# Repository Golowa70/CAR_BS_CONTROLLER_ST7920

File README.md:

# CAR_BS_CONTROLLER_ST7920
Контроллер дополнительного 
оборудования автомобиля описанного в https://github.com/Golowa70/CAR-BS-CONTROLLER-NEX
Используется то же железо но вместо nextion применён дисплей ST7920 + три кнопки
для навигации по меню.

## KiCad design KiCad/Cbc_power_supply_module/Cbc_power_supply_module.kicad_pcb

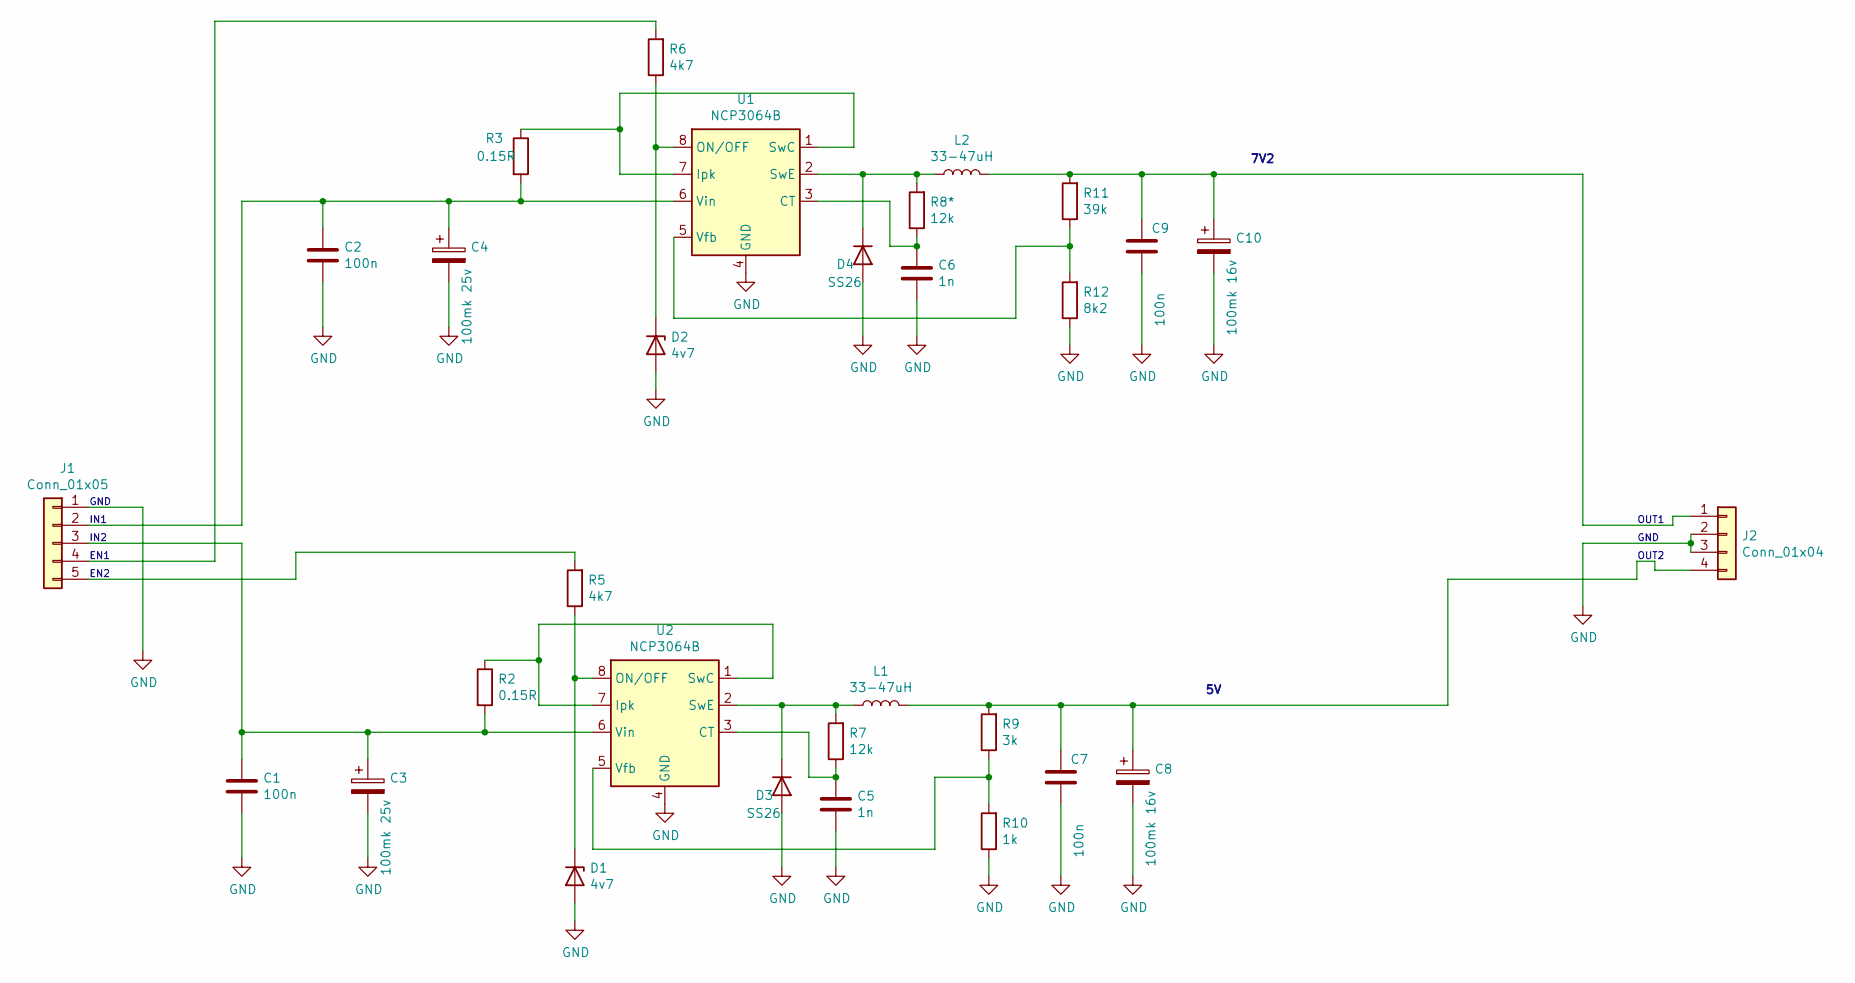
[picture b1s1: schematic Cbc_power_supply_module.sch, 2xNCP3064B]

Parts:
C1, C2, C7, C9: 100n; C_0805_2012Metric_Pad1.18x1.45mm_HandSolder
C3, C4: 100mk 25v; CP_Radial_D8.0mm_P3.80mm
C5, C6: 1n; C_0805_2012Metric_Pad1.18x1.45mm_HandSolder
C8, C10: 100mk 16v; CP_Radial_D8.0mm_P3.80mm
D1, D2: 4v7; D_MiniMELF
D3, D4: SS26; D_SMB
J1: Conn_01x05; PinHeader_1x05_P2.54mm_Vertical
J2: Conn_01x04; PinHeader_1x04_P2.54mm_Vertical
L1, L2: 33-47uH; L_7.3x7.3_H4.5
R2, R3: 0.15R; R_1210_3225Metric_Pad1.30x2.65mm_HandSolder
R5, R6: 4k7; R_0603_1608Metric_Pad0.98x0.95mm_HandSolder
R7, R8*: 12k; R_0805_2012Metric_Pad1.20x1.40mm_HandSolder
R9: 3k; R_0805_2012Metric_Pad1.20x1.40mm_HandSolder
R10: 1k; R_0805_2012Metric_Pad1.20x1.40mm_HandSolder
R11: 39k; R_0805_2012Metric_Pad1.20x1.40mm_HandSolder
R12: 8k2; R_0805_2012Metric_Pad1.20x1.40mm_HandSolder
U1, U2: NCP3064B; SOIC-8_3.9x4.9mm_P1.27mm

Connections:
GND: C1.2, C2.2, C3.2, C4.2, C5.2, C6.2, C7.2, C8.2, C9.2, C10.2, D1.2 (A), D2.2 (A), D3.2 (A), D4.2 (A), J1.1, J2.2, J2.3, R10.1, R12.1, U1.4 (GND), U2.4 (GND)
unnamed: C1.1, C3.1, J1.3, R2.2, U2.6 (Vin)
unnamed: C2.1, C4.1, J1.2, R3.2, U1.6 (Vin)
unnamed: C5.1, R7.1, U2.3 (CT)
unnamed 4: C6.1, R8*.1, U1.3 (CT); also elsewhere on the board
unnamed: C7.1, C8.1, J2.4, L1.2, R9.2
unnamed: C9.1, C10.1, J2.1, L2.2, R11.2
unnamed: D1.1 (K), R5.1, U2.8 (ON/OFF)
unnamed: D2.1 (K), R6.1, U1.8 (ON/OFF)
unnamed: D3.1 (K), L1.1, R7.2, U2.2 (SwE)
unnamed 10: D4.1 (K), L2.1, R8*.2, U1.2 (SwE); also elsewhere on the board
unnamed: J1.4, R6.2
unnamed: J1.5, R5.2
unnamed: R2.1, U2.1 (SwC), U2.7 (Ipk)
unnamed: R3.1, U1.1 (SwC), U1.7 (Ipk)
unnamed: R9.1, R10.2, U2.5 (Vfb)
unnamed: R11.1, R12.2, U1.5 (Vfb)

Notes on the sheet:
7V2
GND
IN1
OUT1
EN1
IN2
OUT2
EN2

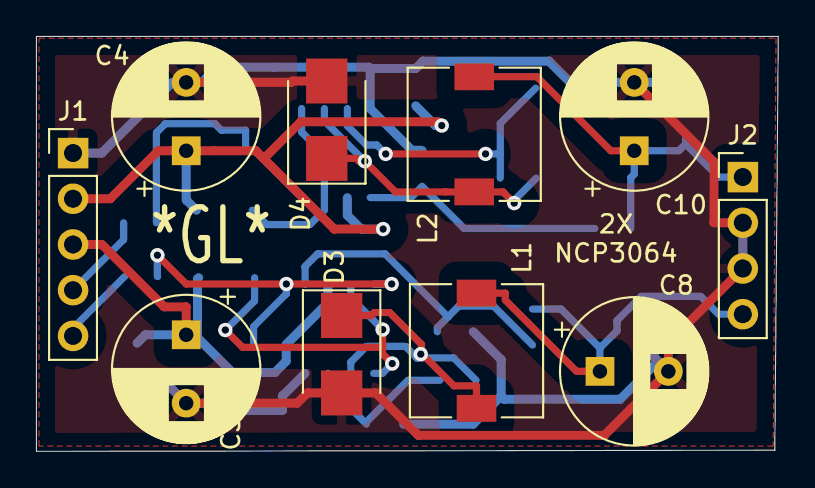
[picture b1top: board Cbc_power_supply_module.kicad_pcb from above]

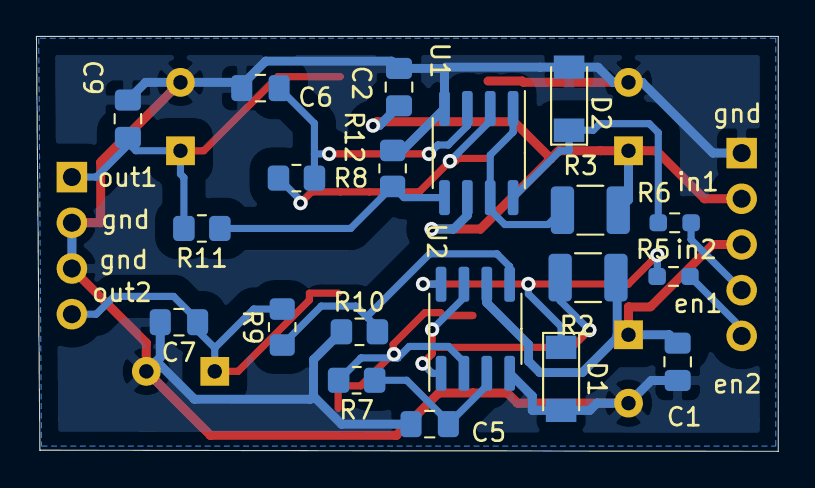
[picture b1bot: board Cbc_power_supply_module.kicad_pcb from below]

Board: 2 copper layers, 41.2 x 23.1 mm, 30 parts (20 on the bottom side), 17 nets.

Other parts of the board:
R8: 12k; R_0805_2012Metric_Pad1.20x1.40mm_HandSolder

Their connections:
unnamed 4: R8.1; also elsewhere on the board
unnamed 10: R8.2; also elsewhere on the board

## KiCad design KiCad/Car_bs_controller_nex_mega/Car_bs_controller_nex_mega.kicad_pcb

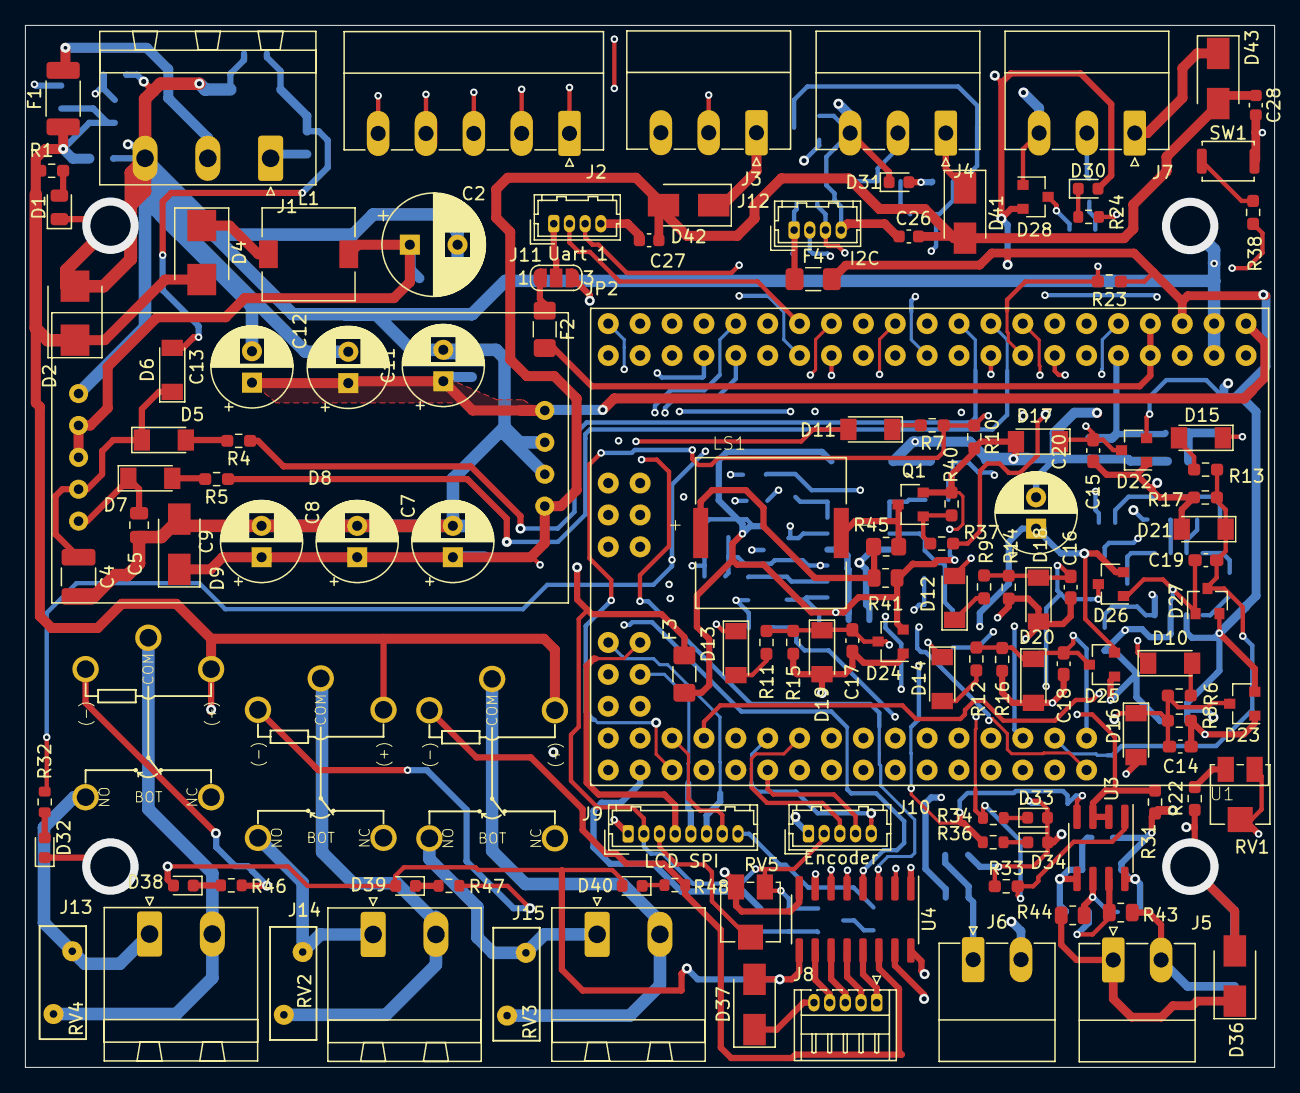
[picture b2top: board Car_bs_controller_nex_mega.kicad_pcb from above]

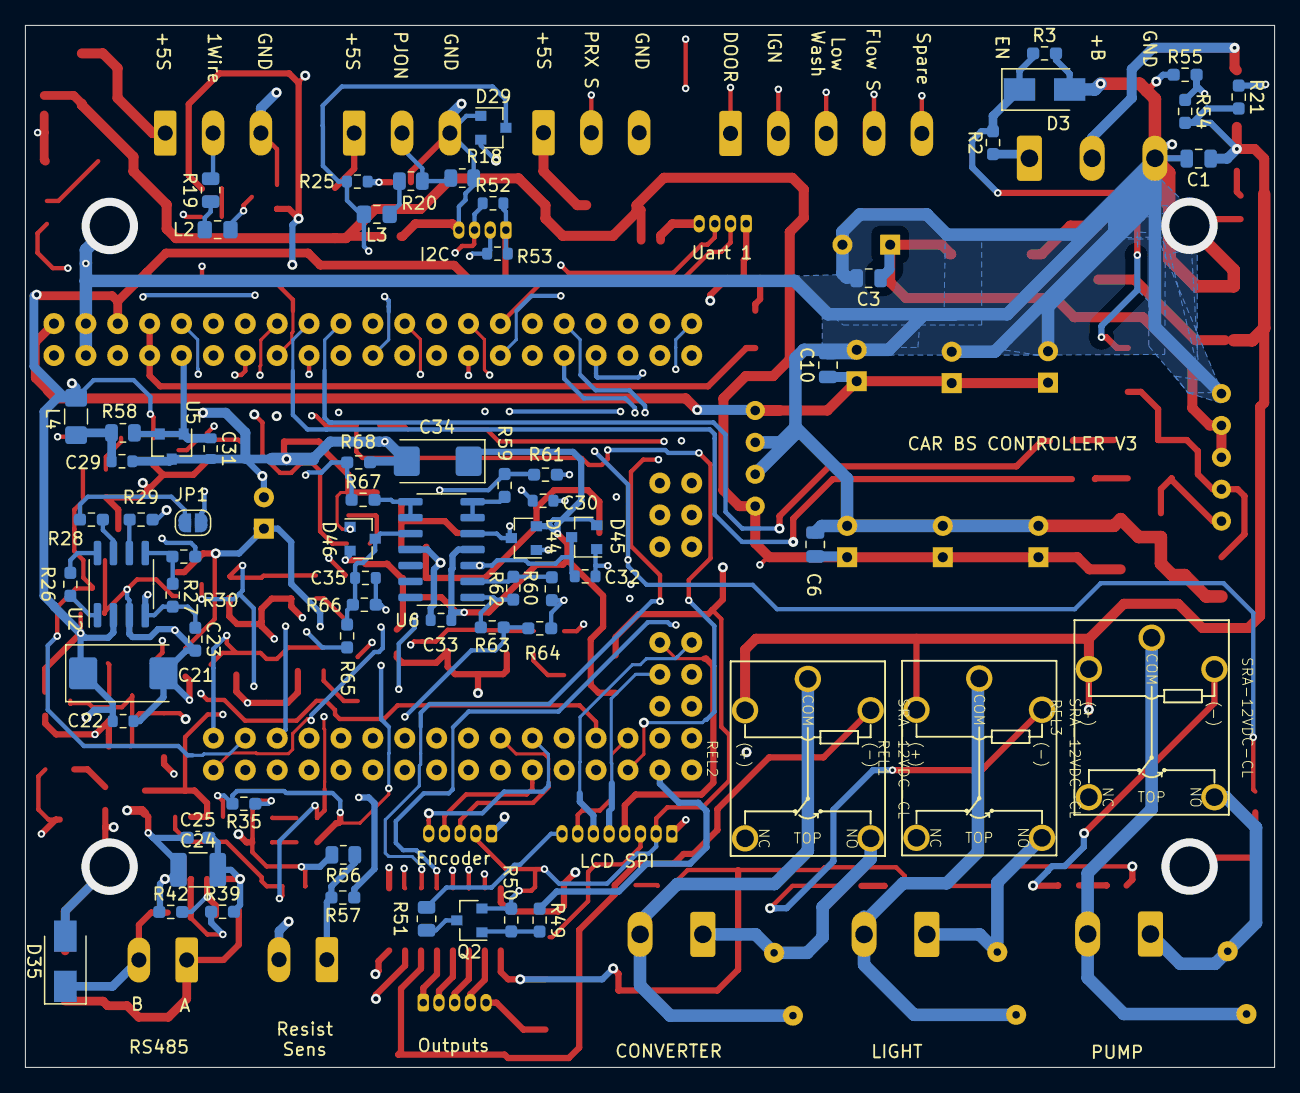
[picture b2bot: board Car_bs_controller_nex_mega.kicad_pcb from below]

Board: 4 copper layers, 99.5 x 83.0 mm, 192 parts (68 on the bottom side), 132 nets.

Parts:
C1, C3, C6, C10: 100n; C_0805_2012Metric
C2: 220mk 25v; CP_Radial_D8.0mm_P3.80mm
C4: 10mk; C_1210_3225Metric_Pad1.33x2.70mm_HandSolder
C5: 1n; C_0805_2012Metric
C7, C8, C9, C20: 220mk 10v; CP_Radial_D6.3mm_P2.50mm
C11, C12, C13: 220mk 16v; CP_Radial_D6.3mm_P2.50mm
C14, C15, C16, C17, C18, C19: 10n; C_0603_1608Metric_Pad1.08x0.95mm_HandSolder
C21: 10mk; CP_EIA-7343-15_Kemet-W_Pad2.25x2.55mm_HandSolder
C22, C29, C31, C33: 100n; R_0603_1608Metric
C23: 1n; R_0603_1608Metric_Pad0.98x0.95mm_HandSolder
C24: 10m; C_1210_3225Metric_Pad1.33x2.70mm_HandSolder
C25: 100n; C_0603_1608Metric_Pad1.08x0.95mm_HandSolder
C26, C27, C28: 100n; C_0603_1608Metric
C30, C32, C35: 10n; R_0603_1608Metric
C34: 10mk; CP_EIA-6032-15_Kemet-U
D1: PWR; LED_0805_2012Metric
D2: SMBJ18CA; D_SMB
D3: SMAJ18CA; D_SMA
D4: SS54; D_SMB
D5, D6, D7: 1N4148; D_MiniMELF
D8: Cbc_power_module
D9: SMBJ5CA; D_SMA
D10, D11, D12, D13, D14, D15: LL4148; D_MiniMELF
D16, D19, D20, D21: N; D_MiniMELF
D17, D18: 4V7; D_MiniMELF
D22, D23, D24, D25, D26, D27, D28, D29, D44, D45, D46: BAV99; SOT-23
D30: LED_1WIRE; LED_0603_1608Metric
D31, D32: LED_PJ; LED_0603_1608Metric
D33, D34: LED; LED_0603_1608Metric
D35, D36: SMAJ5.0CA; D_SMA
D37, D41, D42, D43: SS14; D_SMA
D38: LED_K1; LED_0603_1608Metric
D39: LED_K2; LED_0603_1608Metric
D40: LED_K3; LED_0603_1608Metric
F1: 3A; Fuse_2010_5025Metric
F2, F3, F4: 200mA 5v; Fuse_1206_3216Metric_Pad1.42x1.75mm_HandSolder
J1: Power; PhoenixContact_MSTBA_2,5_3-G_1x03_P5.00mm_Horizontal
J2: Inputs; PhoenixContact_MC_1,5_5-G-3.81_1x05_P3.81mm_Horizontal
J3: Proxy; PhoenixContact_MC_1,5_3-G-3.81_1x03_P3.81mm_Horizontal
J4: PJON; PhoenixContact_MC_1,5_3-G-3.81_1x03_P3.81mm_Horizontal
J5: RS485; PhoenixContact_MC_1,5_2-G-3.81_1x02_P3.81mm_Horizontal
J6: RES_SENS; PhoenixContact_MC_1,5_2-G-3.81_1x02_P3.81mm_Horizontal
J7: 1_WARE; PhoenixContact_MC_1,5_3-G-3.81_1x03_P3.81mm_Horizontal
J8: Outputs; Hirose_DF13-05P-1.25DS_1x05_P1.25mm_Horizontal
J9: LCD_ST7920; Hirose_DF13-08P-1.25DSA_1x08_P1.25mm_Vertical
J10: Encoder; Hirose_DF13-05P-1.25DSA_1x05_P1.25mm_Vertical
J11: LCD_Nextion; Hirose_DF13-04P-1.25DSA_1x04_P1.25mm_Vertical
J12: I2C; Hirose_DF13-04P-1.25DSA_1x04_P1.25mm_Vertical
J13: PUMP_RELAY; PhoenixContact_MSTBA_2,5_2-G_1x02_P5.00mm_Horizontal
J14: LIGHT_RELAY; PhoenixContact_MSTBA_2,5_2-G_1x02_P5.00mm_Horizontal
J15: CONVERTER_RELAY; PhoenixContact_MSTBA_2,5_2-G_1x02_P5.00mm_Horizontal
JP1: SolderJumper_2_Open; SolderJumper-2_P1.3mm_Open_RoundedPad1.0x1.5mm
JP2: SolderJumper_3_Open; SolderJumper-3_P1.3mm_Open_RoundedPad1.0x1.5mm_NumberLabels
L1: 47uH; L_7.3x7.3_H4.5
L2, L3: BLN; L_0805_2012Metric_Pad1.15x1.40mm_HandSolder
L4: FB; L_1206_3216Metric_Pad1.42x1.75mm_HandSolder
LS1: PKLCS1212E4001-R1; SPKR_PKLCS1212E4001-R1
Q1: BSS138; SOT-23
Q2: BC857; SOT-23
R1: 3k9; R_0603_1608Metric_Pad0.98x0.95mm_HandSolder
R2, R4, R5: 2k; R_0603_1608Metric_Pad0.98x0.95mm_HandSolder
R3, R30, R37, R49: 1k; R_0603_1608Metric_Pad0.98x0.95mm_HandSolder
R6, R11, R12, R13, R23: 4k7; R_0603_1608Metric_Pad0.98x0.95mm_HandSolder
R7, R9: 15k; R_0603_1608Metric_Pad0.98x0.95mm_HandSolder
R8, R15, R16, R17: N; R_0603_1608Metric_Pad0.98x0.95mm_HandSolder
R10, R14, R31, R33, R35, R40, R50, R55, R57, R61, R66, R68: 10k; R_0603_1608Metric_Pad0.98x0.95mm_HandSolder
R18: 1M; R_0805_2012Metric
R19, R41: 22R; R_0805_2012Metric
R20: 180R; R_0805_2012Metric
R21, R65: 22k; R_0603_1608Metric_Pad0.98x0.95mm_HandSolder
R22, R29, R60: 2k2; R_0603_1608Metric_Pad0.98x0.95mm_HandSolder
R24, R25, R32, R52, R53: 2k2; R_0603_1608Metric
R26: 200R; R_0603_1608Metric_Pad0.98x0.95mm_HandSolder
R27: (not used) 1k; R_0603_1608Metric_Pad0.98x0.95mm_HandSolder
R28: 220R; R_0603_1608Metric_Pad0.98x0.95mm_HandSolder
R34, R36: 1k; R_0603_1608Metric
R38: 470R; R_0603_1608Metric_Pad0.98x0.95mm_HandSolder
R39, R42: 20k; R_0603_1608Metric_Pad0.98x0.95mm_HandSolder
R43, R44: 10R; R_0805_2012Metric
R45: 1k; R_0805_2012Metric_Pad1.20x1.40mm_HandSolder
R46, R47, R48: 10k; R_0603_1608Metric
R51: 220R; R_0805_2012Metric
R54: 39k; R_0603_1608Metric_Pad0.98x0.95mm_HandSolder
R56: 2k*; R_0805_2012Metric
R58: 330R; R_0805_2012Metric
R59, R63, R67: 6k8; R_0603_1608Metric_Pad0.98x0.95mm_HandSolder
R62: 10k*; R_0603_1608Metric_Pad0.98x0.95mm_HandSolder
R64: 15k*; R_0603_1608Metric_Pad0.98x0.95mm_HandSolder
REL1, REL2, REL3: SRA-12VDC-CL; AB2_SRA-12VDC-CL
RV1, RV5: 10k; Potentiometer_Bourns_3314J_Vertical
RV2, RV3, RV4: S07K17; RV_Disc_D9mm_W3.7mm_P5mm
SW1: SW_Push; SW_Push_SPST_NO_Alps_SKRK
U1: MEGA_PRO_EMBED_CH340G___ATMEGA2560; _ATMEGA2560
U2: ADM705; SOIC-8_3.9x4.9mm_P1.27mm
U3: MAX485E; SOIC-8_3.9x4.9mm_P1.27mm
U4: ULN2003A; SOIC-16_3.9x9.9mm_P1.27mm
U5: TL431DBZ; SOT-23
U6: MCP6004(LM324); SOIC-14_3.9x8.7mm_P1.27mm

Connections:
5V_sensors_stab: C6.1, C7.1, C8.1, C9.1, C26.1, C27.1, C28.1, D8.9, D9.1, D41.1, D42.1, D43.1, R65.2
7.2V_stab: C10.1, C11.1, C12.1, C13.1, D8.6, U1.VIN_1
+3v3_from_MCU: F2.2, U1.3V3_1, U1.3V3_2
+5v_FROM_MCU: C20.1, C21.1, C22.1, C24.1, C25.1, C33.1, C34.1, D22.2, D23.2, D24.2, D25.2, D26.2, D27.2, D28.2, D29.2, D30.2, D33.2, D34.2, D44.2, D45.2, D46.2, F3.2, F4.2, L4.1, R23.1, R31.1, R33.1, R35.1, R41.2, R42.1, R56.2, U1.5V_1, U2.2, U3.8, U6.4
+12V: C1.1, D2.1, D4.2, D37.1, D38.2, D39.2, D40.2, F1.1, R1.2, R21.2, R54.2, REL1.1, REL2.1, REL3.1, U4.9
CONVERTER_RELAY_COM: J15.2, REL2.3, RV3.1
CONVERTER_RELAY_NO: J15.1, REL2.5, RV3.2
DOOR_SWITCH_INPUT: D13.1, J2.1
GND: C1.2, C2.2, C3.2, C4.2, C5.2, C6.2, C7.2, C8.2, C9.2, C10.2, C11.2, C12.2, C13.2, C14.2, C15.2, C16.2, C17.2, C18.2, C19.2, C20.2, C21.2, C22.2, C23.2, C24.2, C25.2, C26.2, C27.2, C28.2, C29.2, C30.2, C31.2, C32.2, C33.2, C34.2, C35.2, D1.1, D2.2, D3.2, D8.1, D8.7, D8.8, D9.2, D16.2, D17.2, D18.2, D19.2, D20.2, D21.2, D22.1, D23.1, D24.1, D25.1, D26.1, D27.1, D28.1, D29.1, D31.1, D32.1, D35.2, D36.2, D44.1, D45.1, D46.1, J1.3, J3.3, J4.3, J6.2, J7.3, J9.1, J10.1, J11.4, J12.4, Q1.2, R3.2, R8.2, R10.2, R14.2, R15.2, R16.2, R17.2, R18.2, R22.2, R39.2, R40.2, R55.1, R60.1, R61.1, R64.1, R66.1, R68.1, RV5.3, SW1.2, U1.GND_1, U1.GND_2, U1.GND_3, U2.3, U3.5, U4.8, U5.3, U6.11
IGNITION_SWITCH_INPUT: D12.2, J2.2
LCD_BLA: R49.1, U1.D44
LCD_DI_MCU_CS: J9.4, U1.D53
LCD_E_MCU_SCLK: J9.6, U1.D52
LCD_RST: J9.7, U1.D43
LCD_RW_MCU_MOSI: J9.5, U1.D51
LIGHT_RELAY_COM: J14.2, REL1.3, RV2.1
LIGHT_RELAY_NO: J14.1, REL1.5, RV2.2
LOW_WASHER_WATER_LEVEL_INPUT: D15.1, J2.3
MCU_5V_sensors_enable: R5.1, U1.D7
MCU_I2C_SCL: J12.3, R52.1, U1.D21
MCU_I2C_SDA: J12.2, R53.1, U1.D20
MCU_UART1_RX: J11.2, U1.D19
MCU_UART1_TX: J11.3, U1.D18
MCU_UART2_RX: R33.2, R34.1, U1.D17, U3.1
MCU_UART2_TX: R35.2, R36.1, U1.D16, U3.4
MCU_Uref_2.5v: C31.1, R58.1, U1.AREF, U5.1, U5.2
MCU_button_on_board: R38.2, U1.D10
MCU_buzzer_out: R37.2, U1.D2
MCU_converter_out: U1.D24, U4.3
MCU_door_switch_input: C17.1, D19.1, D24.3, R11.1, R15.1, U1.A0
MCU_encoder_CLK: J10.5, U1.D37
MCU_encoder_DT: J10.4, U1.D36
MCU_encoder_SW: J10.3, U1.D35
MCU_ignition_switch_input: C16.1, D18.1, D26.3, R9.1, R14.1, U1.A2
MCU_light_out: U1.D23, U4.2
MCU_low_washer_water_level_input: C19.1, D21.1, D27.3, R13.1, R17.1, U1.A3
MCU_main_supply_enable: R4.1, U1.D9
MCU_one_wire_PIN: D28.3, L2.2, R23.2, R24.2, U1.D4
MCU_pjon_bus_PIN: D29.3, L3.2, R25.1, U1.D3
MCU_power_OK_from_ADM705: R30.1, U1.D41
MCU_proximity_input: C18.1, D20.1, D25.3, R12.1, R16.1, U1.A1
MCU_resistive_sensor_0_190: R63.1, R64.2, U1.A6
MCU_rs485_de: R31.2, U1.D6, U3.2, U3.3
MCU_rst: JP1.2, U1.RST
MCU_sensors_voltage_test_input: R67.1, R68.2, U1.A5
MCU_spare_input_1: C15.1, D17.1, D22.3, R7.1, R10.1, U1.D42
MCU_spare_out_1: U1.D31, U4.4
MCU_spare_out_2: U1.D32, U4.5
MCU_spare_out_3: U1.D33, U4.6
MCU_spare_out_4: U1.D34, U4.7
MCU_supply_voltage_input: R59.1, R61.2, U1.A4
MCU_system_status_LED: R32.1, U1.D13
MCU_water_flow_sensor: C14.1, D16.1, D23.3, R6.1, R8.1, U1.D5
MCU_water_pump_out: U1.D22, U4.1
MCU_wdt_reset_to_ADM705: R29.1, U1.D8
unnamed: C2.1, C3.1, D8.2, D8.3, L1.2
unnamed: C4.1, D5.1, D6.1, D8.4
unnamed: C5.1, D7.1, D8.5
unnamed: C23.1, R21.1, R27.2, RV1.1, RV1.2, U2.4
unnamed: C29.1, L4.2, R58.2
unnamed: C30.1, D44.3, R54.1, R55.2, U6.5
unnamed: C32.1, D45.3, R57.1, U6.3
unnamed: C35.1, D46.3, R65.1, R66.2, U6.10
unnamed: D1.2, R1.1
unnamed: D3.1, D6.2, R2.2, R3.1
unnamed: D4.1, L1.1
unnamed: D5.2, R4.2
unnamed: D7.2, R5.2
unnamed: D10.2, R6.2
unnamed: D11.1, R7.2
unnamed: D12.1, R9.2
unnamed: D13.2, R11.2
unnamed: D14.2, R12.2
unnamed: D15.2, R13.2
unnamed: D30.1, R24.1
unnamed: D31.2, R25.2
unnamed: D32.2, R32.2
unnamed: D33.1, R34.2
unnamed: D34.1, R36.2
unnamed: D38.1, R46.2
unnamed: D39.1, R47.2
unnamed: D40.1, R48.2
unnamed: D41.2, J4.1
unnamed: D42.2, J3.1
unnamed: D43.2, J7.1
unnamed: F2.1, JP2.1
unnamed: F3.1, J9.2, J10.2, JP2.3, Q2.2, R50.2, RV5.1
unnamed: F4.1, J12.1, R52.2, R53.2
unnamed: J9.3, RV5.2
unnamed: J9.8, R51.2
unnamed: J11.1, JP2.2
unnamed: JP1.1, R28.1
unnamed: L2.1, R19.1
unnamed: L3.1, R20.1
unnamed: LS1.N, Q1.3, R45.2
unnamed: LS1.P, R41.1, R45.1
unnamed: Q1.1, R37.1, R40.1
unnamed: Q2.1, R49.2, R50.1
unnamed: Q2.3, R51.1
unnamed: R22.1, RV1.3
unnamed: R26.1, U2.8
unnamed: R26.2, U2.1
unnamed: R27.1, R30.2, U2.5
unnamed: R28.2, U2.7
unnamed: R29.2, U2.6
unnamed: R38.1, SW1.1
unnamed: R39.1, R43.2, U3.7
unnamed: R42.2, R44.2, U3.6
unnamed: R46.1, REL3.2, U4.16
unnamed: R47.1, REL1.2, U4.15
unnamed: R48.1, REL2.2, U4.14
unnamed: R59.2, U6.6, U6.7
unnamed: R60.2, R62.2, U6.2
unnamed: R62.1, R63.2, U6.1
unnamed: R67.2, U6.8, U6.9
ONE_WARE_INPUT: J7.2, R19.2
PJON_BUS: J4.2, R18.1, R20.2
PROXIMITY_SENSOR_INPUT: D14.1, J3.2
PUMP_RELAY_COM: J13.2, REL3.3, RV4.1
PUMP_RELAY_NO: J13.1, REL3.5, RV4.2
Power_enable(ACC,BUTTON): J1.1, R2.1
Power_supply_12V: F1.2, J1.2
RESISTIVE_SENSOR_0_190: J6.1, R56.1, R57.2
RS485_A: D36.1, J5.1, R44.1
RS485_B: D35.1, J5.2, R43.1
SPARE_INPUT_1: D11.2, J2.5
Socket_spare_out_1: J8.1, U4.13
Socket_spare_out_2: J8.2, U4.12
Socket_spare_out_3: J8.3, U4.11
Socket_spare_out_4: J8.4, U4.10
Socket_spare_out_+12v: D37.2, J8.5
WATER_FLOW_SENSOR_INPUT: D10.1, J2.4

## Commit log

2021-12-02 added firmware v1.0
2021-12-02 Added modbus connection status
